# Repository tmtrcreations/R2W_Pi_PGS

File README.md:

# R2W_Pi_PGS
Open source handheld gaming device based on the Raspberry Pi CM3L

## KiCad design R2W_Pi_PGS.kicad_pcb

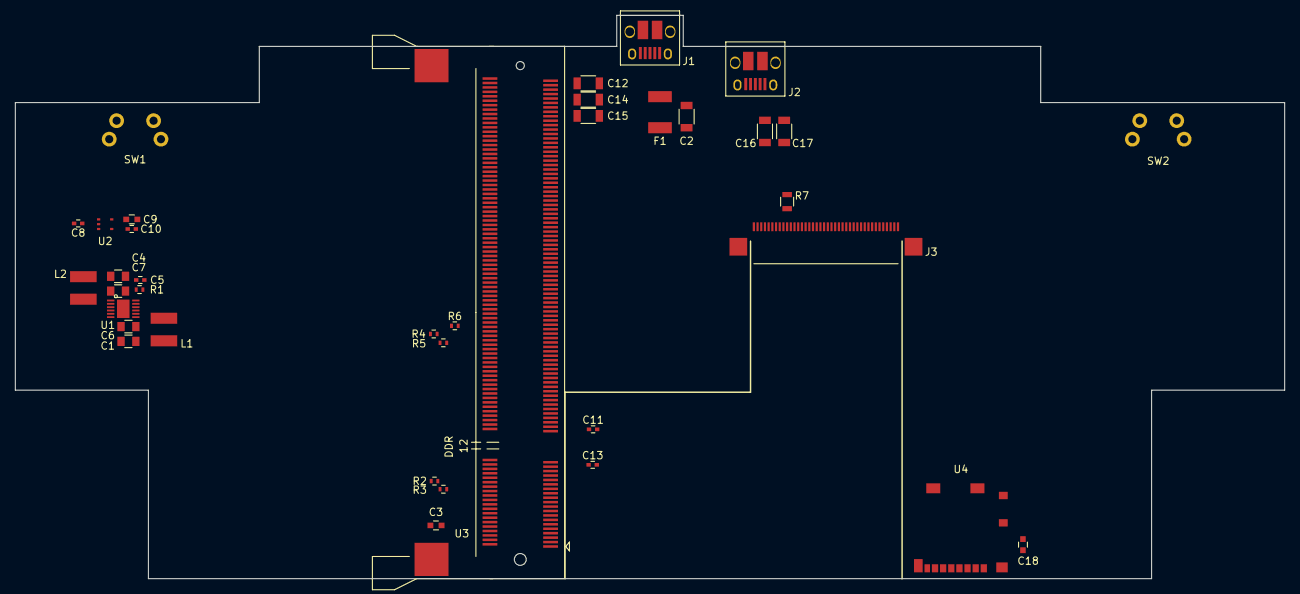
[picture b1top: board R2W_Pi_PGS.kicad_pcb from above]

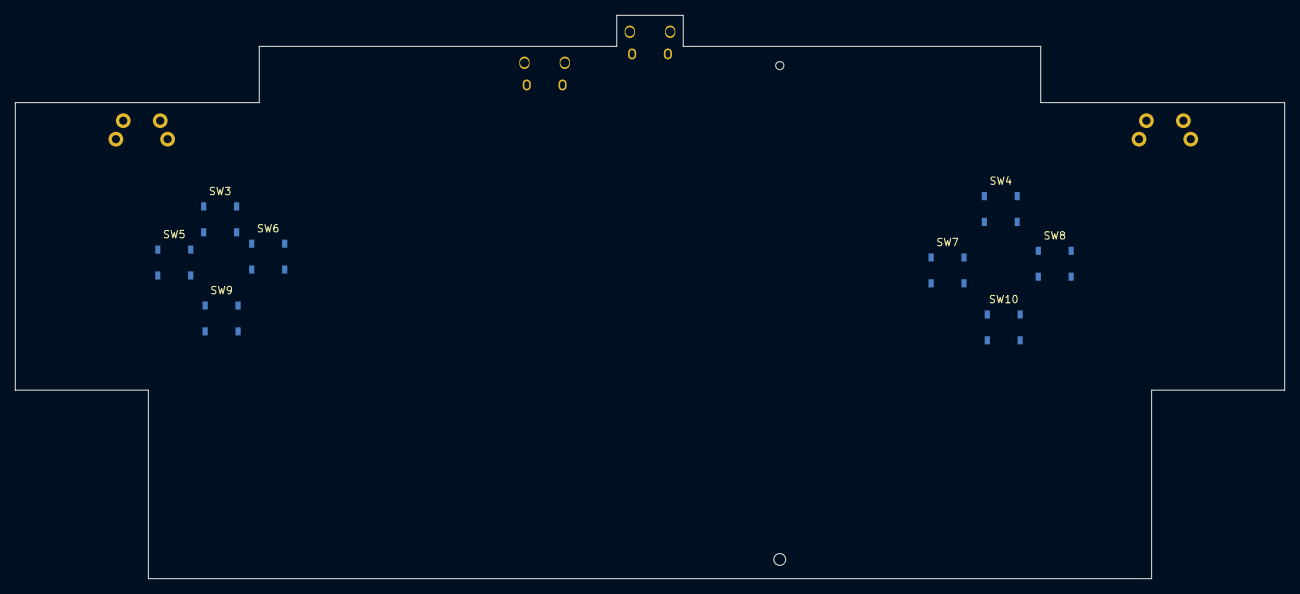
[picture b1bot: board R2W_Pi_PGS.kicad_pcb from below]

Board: 2 copper layers, 171.7 x 76.2 mm, 45 parts (8 on the bottom side), 52 nets, no tracks yet.

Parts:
C1, C4, C6, C7: 10uF; C_0805
C2, C12, C14, C15, C16, C17: 47uF; C_1206
C3, C9, C18: 4.7uF; C_0603
C5, C10: 100nF; C_0402
C8, C11, C13: 1uF; C_0402
F1: MF-MSMF200
J1, J2: USB_OTG; USB_Micro-B_10103594-0001LF
J3: 40_Pin_LCD; LCD_Molex_Connector
L1, L2: 4.7uH; SRN4018-4R7M
R1, R2, R3, R4, R5, R6: 100k; R_0402
R7: 10k; R_0805
SW1: R_BUMP; Tact-switch_right_thru_hole
SW2: L_BUMP; Tact-switch_right_thru_hole
SW3: UP; E-SW_SMD
SW4: X; E-SW_SMD
SW5: LEFT; E-SW_SMD
SW6: RIGHT; E-SW_SMD
SW7: Y; E-SW_SMD
SW8: A; E-SW_SMD
SW9: DOWN; E-SW_SMD
SW10: B; E-SW_SMD
U1: PAM2306AYPKE
U2: AP7115-25SEG; AP7115-25SEG-7
U3: DDR2_SODIMM_CM_3_Lite; Socket_SODIMM_DDR2
U4: 1040310811; uSD_1040310811

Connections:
1V8: C4.1, C15.1, L2.2, R6.2, U1.10, U3.183, U3.184, U3.185, U3.186
3V3: C1.1, C3.1, C8.1, C11.1, C13.1, C14.1, C18.1, J3.4, L1.2, R7.1, U1.4, U2.1, U2.3, U3.2, U3.4, U3.6, U3.39, U3.40, U3.41, U3.42, U3.191, U3.192, U3.193, U3.194, U4.4
5V: C2.1, C6.1, C7.1, C12.1, C16.1, C17.1, F1.2, J2.1, R1.1, U1.1, U1.6, U1.7, U3.197, U3.198, U3.199, U3.200
B0: J3.21, U3.15
B1: J3.22, U3.17
B2: J3.23, U3.21
B3: J3.24, U3.23
B4: J3.25, U3.27
B5: J3.26, U3.29
B6: J3.27, U3.33
B7: J3.28, U3.35
CM_VDAC: C9.1, U2.5, U3.189, U3.190
DE: J3.34, U3.5
G0: J3.13, U3.45
G1: J3.14, U3.47
G2: J3.15, U3.51
G3: J3.16, U3.53
G4: J3.17, U3.57
G5: J3.18, U3.59
G6: J3.19, U3.63
G7: J3.20, U3.65
GND: C1.2, C2.2, C3.2, C4.2, C5.2, C6.2, C7.2, C8.2, C9.2, C10.2, C11.2, C12.2, C13.2, C14.2, C15.2, C16.2, C17.2, C18.2, J1.5, J1.6, J2.5, J2.6, J3.3, J3.29, J3.36, R2.2, R3.2, R4.2, R5.2, U1.3, U1.9, U1.13, U2.2, U3.1, U3.7, U3.8, U3.13, U3.14, U3.19, U3.20, U3.25, U3.26, U3.31, U3.32, U3.37, U3.38, U3.43, U3.44, U3.49, U3.50, U3.55, U3.56, U3.61, U3.62, U3.67, U3.68, U3.73, U3.74, U3.79, U3.80, U3.85, U3.86, U3.91, U3.92, U3.97, U3.98, U3.103, U3.104, U3.109, U3.110, U3.115, U3.116, U3.121, U3.122, U3.127, U3.133, U3.134, U3.139, U3.140, U3.145, U3.146, U3.151, U3.152, U3.157, U3.163, U3.164, U3.169, U3.170, U3.181, U3.182, U3.187, U3.188, U3.195, U3.196, U4.6, U4.11, U4.12, U4.13, U4.14
HSYNC: J3.32, U3.11
unnamed: C5.1, R1.2, U1.12
unnamed: C10.1, U2.4
unnamed: F1.1, J1.1
unnamed: J3.31, R7.2
unnamed: L1.1, U1.8
unnamed: L2.1, U1.2
unnamed: R2.1, U3.30
unnamed: R3.1, U3.28
unnamed: R4.1, U3.84
unnamed: R5.1, U3.82
unnamed: R6.1, U3.88
ODCK: J3.30, U3.3
R0: J3.5, U3.69
R1: J3.6, U3.71
R2: J3.7, U3.75
R3: J3.8, U3.77
R4: J3.9, U3.81
R5: J3.10, U3.83
R6: J3.11, U3.87
R7: J3.12, U3.89
SDX_CLK: U3.10, U4.5
SDX_CMD: U3.12, U4.3
SDX_D0: U3.16, U4.7
SDX_D1: U3.18, U4.8
SDX_D2: U3.22, U4.1
SDX_D3: U3.24, U4.2
USB_D+: J2.3, U3.165
USB_D-: J2.2, U3.167
VSYNC: J3.33, U3.9

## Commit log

2018-09-08 Initial push
2018-09-08 File rename
2018-09-09 Added screen and buttons
